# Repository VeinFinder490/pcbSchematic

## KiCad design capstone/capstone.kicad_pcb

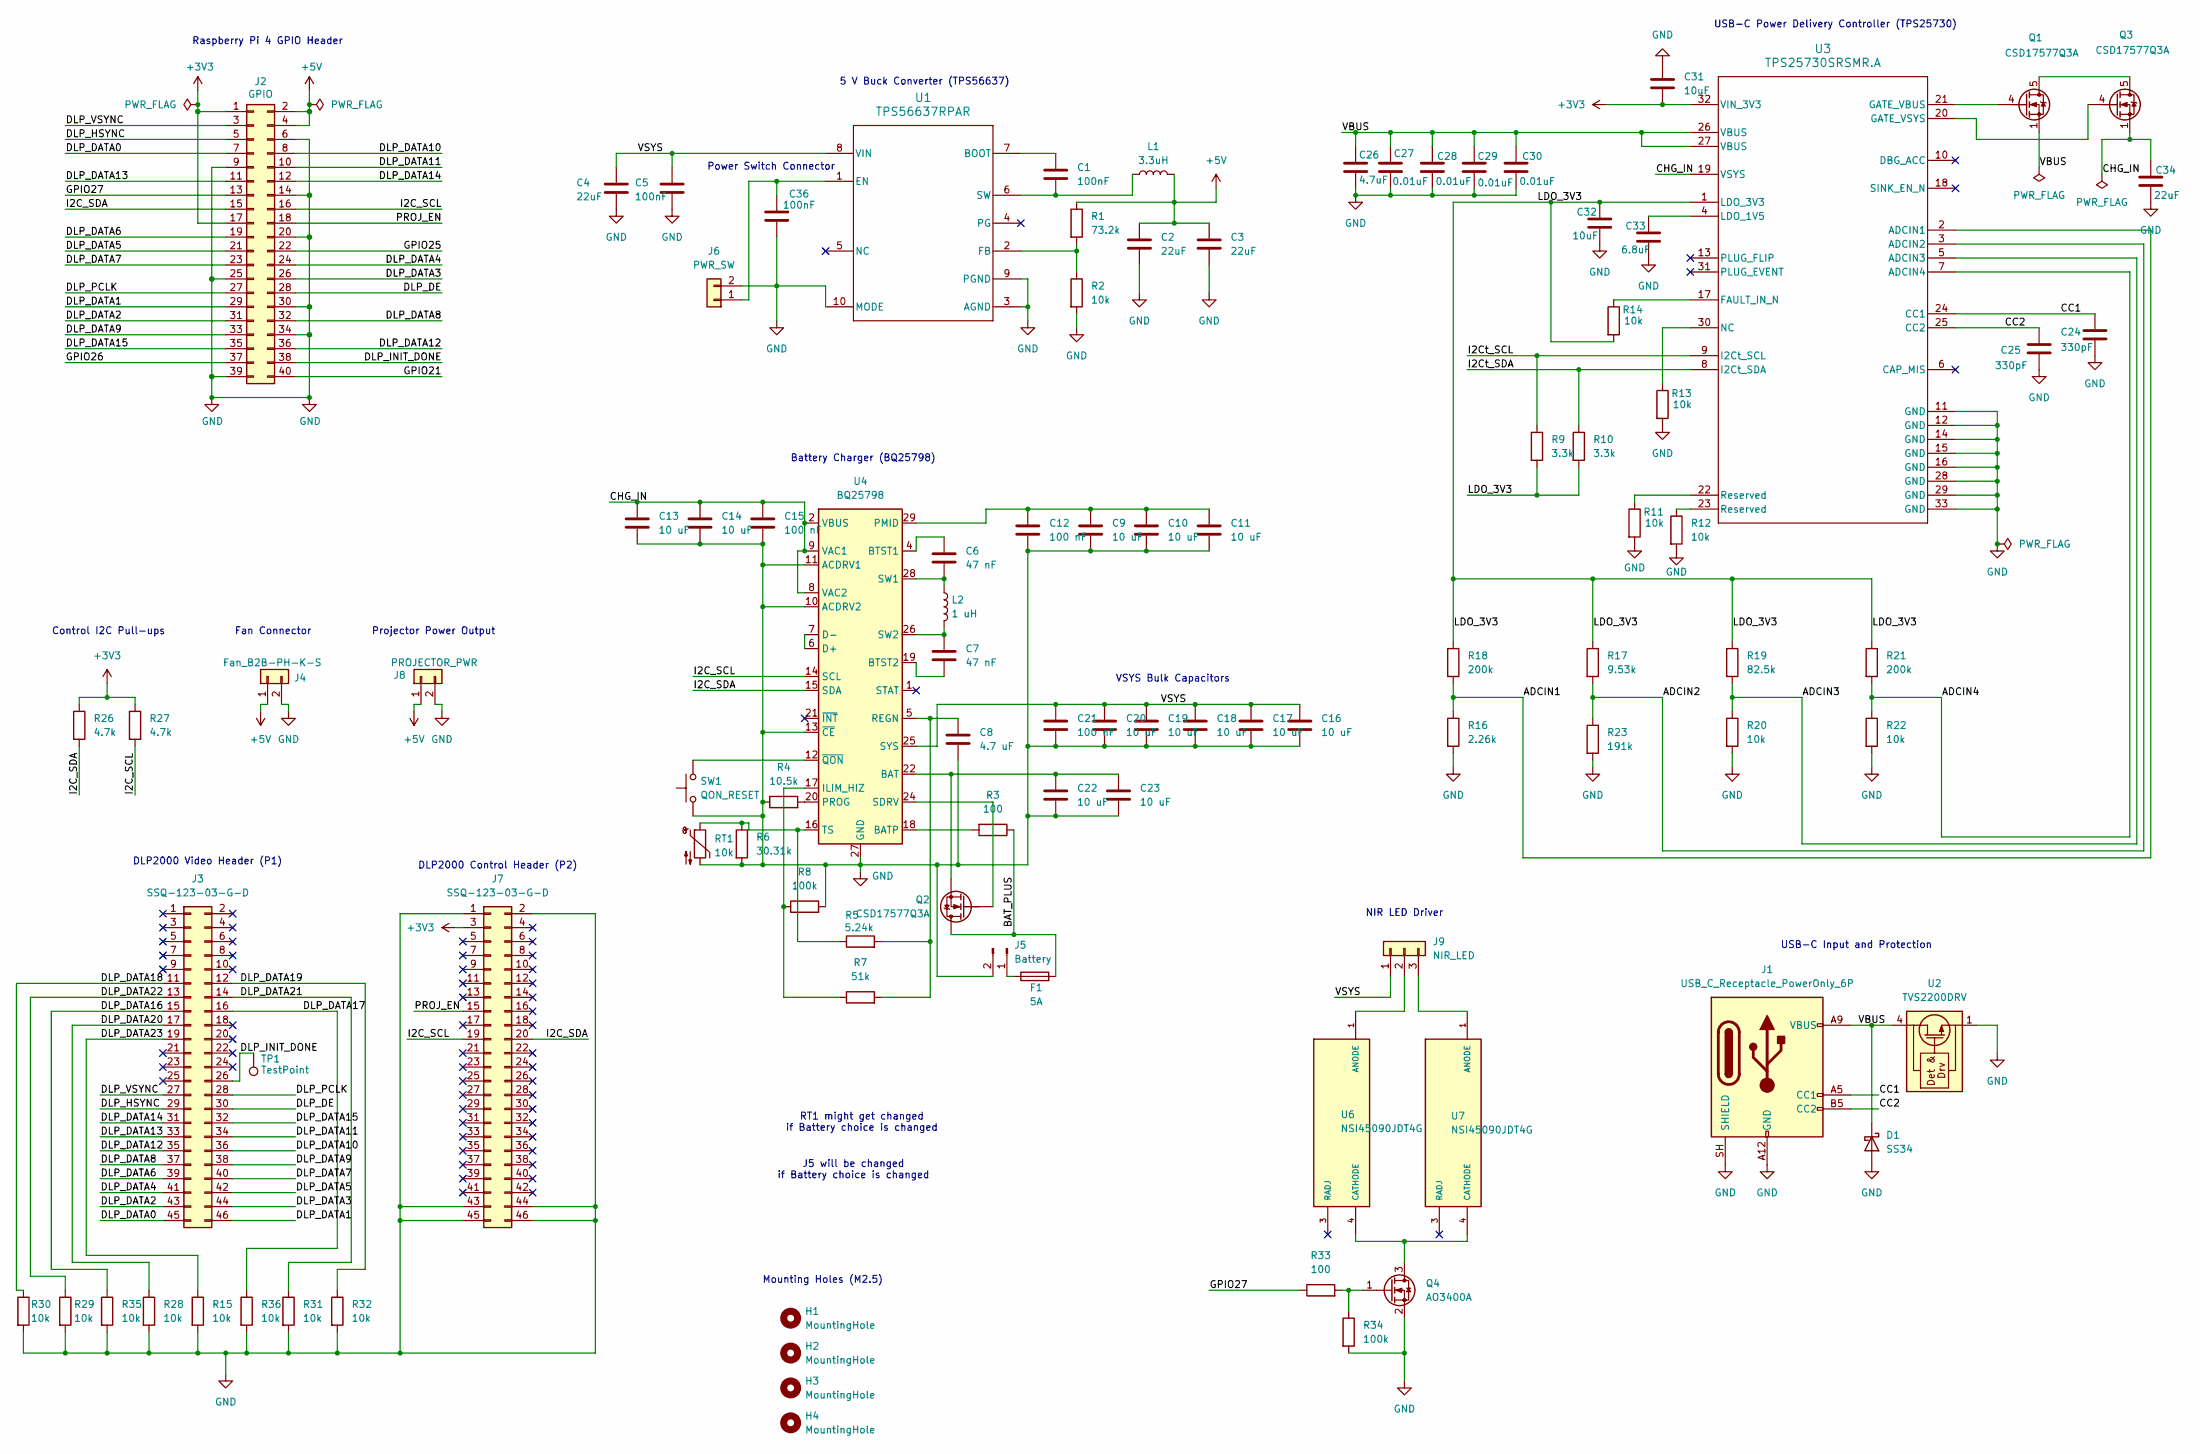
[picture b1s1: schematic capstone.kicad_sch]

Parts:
C1, C5, C36: 100nF; C_0805_2012Metric
C2, C3: 22uF; C_1210_3225Metric
C4, C34: 22uF; C_2220_5750Metric
C6, C7: 47 nF; C_0805_2012Metric
C8: 4.7 uF; C_1206_3216Metric
C9, C10, C11, C13, C14, C16, C17, C18, C19, C20, C22, C23: 10 uF; C_1210_3225Metric
C12, C15, C21: 100 nF; C_0805_2012Metric
C24, C25: 330pF; C_0805_2012Metric
C26: 4.7uF; C_1206_3216Metric
C27, C28, C29, C30: 0.01uF; C_0805_2012Metric
C31, C32: 10uF; C_1210_3225Metric
C33: 6.8uF; C_1206_3216Metric
D1: SS34; D_SMA
F1: 5A; Fuse_1206_3216Metric
H1, H2, H3, H4: MountingHole; MountingHole_2.7mm_M2.5
J1: USB_C_Receptacle_PowerOnly_6P; USB_C_Receptacle_GCT_USB4125-xx-x_6P_TopMnt_Horizontal
J2: GPIO; PinSocket_2x20_P2.54mm_Vertical
J3, J7: SSQ-123-03-G-D; PinHeader_2x23_P2.54mm_Vertical
J4: Fan_B2B-PH-K-S; JST_PH_B2B-PH-K_1x02_P2.00mm_Vertical
J5: Battery; JST_XH_B2B-XH-A_1x02_P2.50mm_Vertical
J6: PWR_SW; JST_PH_B2B-PH-K_1x02_P2.00mm_Vertical
J8: PROJECTOR_PWR; JST_PH_B2B-PH-K_1x02_P2.00mm_Vertical
J9: NIR_LED; JST_PH_B3B-PH-K_1x03_P2.00mm_Vertical
L1: 3.3uH; L_Coilcraft_XAL7030-332
L2: 1 uH; L_Coilcraft_XAL7030-102
Q1, Q2, Q3: CSD17577Q3A; VSON-8_3.3x3.3mm_P0.65mm_NexFET
Q4: AO3400A; SOT-23
R1: 73.2k; R_0805_2012Metric
R2, R11, R12, R13, R14, R15, R20, R22, R28, R29, R30, R31, R32, R35, R36: 10k; R_0805_2012Metric
R3, R33: 100; R_0805_2012Metric
R4: 10.5k; R_0805_2012Metric
R5: 5.24k; R_0805_2012Metric
R6: 30.31k; R_0805_2012Metric
R7: 51k; R_0805_2012Metric
R8, R34: 100k; R_0805_2012Metric
R9, R10: 3.3k; R_0805_2012Metric
R16: 2.26k; R_0805_2012Metric
R17: 9.53k; R_0805_2012Metric
R18, R21: 200k; R_0805_2012Metric
R19: 82.5k; R_0805_2012Metric
R23: 191k; R_0805_2012Metric
R26, R27: 4.7k; R_0805_2012Metric
RT1: 10k; R_0603_1608Metric
SW1: QON_RESET; SW_SPST_PTS645Sx43SMTR92
TP1: TestPoint; TestPoint_Pad_D1.5mm
U1: TPS56637RPAR; RPA0010A
U2: TVS2200DRV; WSON-6-1EP_2x2mm_P0.65mm_EP1x1.6mm
U3: TPS25730SRSMR.A; RSM0032B-IPC_A
U4: BQ25798; Texas_RQM0029A_VQFN-29_4x4mm_P0.4mm
U6, U7: NSI45090JDT4G; IC_NSI45090JDT4G; MPN NSI45090JDT4G

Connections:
+3V3: C31.2, J2.1, J2.17, J7.3, R26.1, R27.1, U3.32 (VIN_3V3)
+5V: C2.1, C3.1, J2.2, J2.4, J4.1, J8.1, L1.2, R1.1
/ADCIN1: R16.1, R18.2, U3.2 (ADCIN1)
/ADCIN2: R17.2, R23.1, U3.3 (ADCIN2)
/ADCIN3: R19.2, R20.1, U3.5 (ADCIN3)
/ADCIN4: R21.2, R22.1, U3.7 (ADCIN4)
/BAT_PLUS: F1.2, Q2.5 (D), R3.1
/CC1: C24.2, J1.A5 (CC1), U3.24 (CC1)
/CC2: C25.2, J1.B5 (CC2), U3.25 (CC2)
/CHG_IN: C13.1, C14.1, C15.1, C34.1, Q3.1 (S), Q3.2 (S), Q3.3 (S), U3.19 (VSYS), U4.2 (VBUS), U4.3 (VBUS), U4.8 (VAC2), U4.9 (VAC1)
/DLP_DATA0: J2.7, J3.45
/DLP_DATA1: J2.29, J3.46
/DLP_DATA2: J2.31, J3.43
/DLP_DATA3: J2.26, J3.44
/DLP_DATA4: J2.24, J3.41
/DLP_DATA5: J2.21, J3.42
/DLP_DATA6: J2.19, J3.39
/DLP_DATA7: J2.23, J3.40
/DLP_DATA8: J2.32, J3.37
/DLP_DATA9: J2.33, J3.38
/DLP_DATA10: J2.8, J3.36
/DLP_DATA11: J2.10, J3.34
/DLP_DATA12: J2.36, J3.35
/DLP_DATA13: J2.11, J3.33
/DLP_DATA14: J2.12, J3.31
/DLP_DATA15: J2.35, J3.32
/DLP_DATA16: J3.15, R35.1
/DLP_DATA17: J3.16, R36.1
/DLP_DATA18: J3.11, R30.1
/DLP_DATA19: J3.12, R32.1
/DLP_DATA20: J3.17, R28.1
/DLP_DATA21: J3.14, R31.1
/DLP_DATA22: J3.13, R29.1
/DLP_DATA23: J3.19, R15.1
/DLP_DE: J2.28, J3.30
/DLP_HSYNC: J2.5, J3.29
/DLP_PCLK: J2.27, J3.28
/DLP_VSYNC: J2.3, J3.27
/GPIO21: J2.40
/GPIO25: J2.22
/GPIO26: J2.37
/GPIO27: J2.13, R33.1
/I2C_SCL: J2.16, J7.19, R27.2, U4.14 (SCL)
/I2C_SDA: J2.15, J7.20, R26.2, U4.15 (SDA)
/I2Ct_SCL: R9.1, U3.9 (I2Ct_SCL)
/I2Ct_SDA: R10.1, U3.8 (I2Ct_SDA)
/LDO_3V3: C32.2, R9.2, R10.2, R14.2, R17.1, R18.1, R19.1, R21.1, U3.1 (LDO_3V3)
/PROJ_EN: J2.18, J7.15
/VBUS: C26.1, C27.1, C28.1, C29.1, C30.1, D1.1 (K), J1.A9 (VBUS), J1.B9 (VBUS), Q1.1 (S), Q1.2 (S), Q1.3 (S), U2.4 (IN), U2.5 (IN), U2.6 (IN), U3.26 (VBUS), U3.27 (VBUS)
/VSYS: C4.1, C5.1, C16.1, C17.1, C18.1, C19.1, C20.1, C21.1, J9.1, U1.8 (VIN), U4.25 (SYS)
GND: C2.2, C3.2, C4.2, C5.2, C8.2, C9.2, C10.2, C11.2, C12.2, C13.2, C14.2, C15.2, C16.2, C17.2, C18.2, C19.2, C20.2, C21.2, C22.2, C23.2, C24.1, C25.1, C26.2, C27.2, C28.2, C29.2, C30.2, C31.1, C32.1, C33.1, C34.2, C36.1, D1.2 (A), J1.A12 (GND), J1.B12 (GND), J1.SH (SHIELD), J2.6, J2.9, J2.14, J2.20, J2.25, J2.30, J2.34, J2.39, J4.2, J5.2, J6.2, J7.1, J7.2, J7.43, J7.44, J7.45, J7.46, J8.2, Q4.2 (S), R2.2, R4.1, R6.2, R8.2, R11.2, R12.2, R13.2, R15.2, R16.2, R20.2, R22.2, R23.2, R28.2, R29.2, R30.2, R31.2, R32.2, R34.2, R35.2, R36.2, RT1.2, SW1.1, U1.3 (AGND), U1.9 (PGND), U1.10 (MODE), U2.1 (GND), U2.2 (GND), U2.3 (GND), U2.7 (GND), U3.11 (GND), U3.12 (GND), U3.14 (GND), U3.15 (GND), U3.16 (GND), U3.28 (GND), U3.29 (GND), U3.33 (GND), U4.10 (ACDRV2), U4.11 (ACDRV1), U4.13 (~CE), U4.27 (GND)
unnamed: C22.1, C23.1, Q2.1 (S), Q2.2 (S), Q2.3 (S), U4.22 (BAT), U4.23 (BAT)
unnamed: F1.1, J5.1
unnamed: C36.2, J6.1, U1.1 (EN)
unnamed: J9.2, U6.1 (ANODE)
unnamed: J9.3, U7.1 (ANODE)
unnamed: Q1.5 (D), Q3.5 (D)
unnamed: Q1.4 (G), U3.21 (GATE_VBUS)
unnamed: Q2.4 (G), U4.24 (SDRV)
unnamed: Q3.4 (G), U3.20 (GATE_VSYS)
unnamed: Q4.3 (D), U6.4 (CATHODE), U7.4 (CATHODE)
unnamed: Q4.1 (G), R33.2, R34.1
unnamed: R11.1, U3.22 (Reserved)
unnamed: R12.1, U3.23 (Reserved)
unnamed: C1.1, U1.7 (BOOT)
unnamed: R1.2, R2.1, U1.2 (FB)
unnamed: C1.2, L1.1, U1.6 (SW)
unnamed: R14.1, U3.17 (FAULT_IN_N)
unnamed: C33.2, U3.4 (LDO_1V5)
unnamed: R13.1, U3.30 (NC)
unnamed: R3.2, U4.18 (BATP)
unnamed: C6.1, U4.4 (BTST1)
unnamed: C7.2, U4.19 (BTST2)
unnamed: R7.1, R8.1, U4.17 (ILIM_HIZ)
unnamed: C9.1, C10.1, C11.1, C12.1, U4.29 (PMID)
unnamed: R4.2, U4.20 (PROG)
unnamed: C8.1, R5.2, R7.2, U4.5 (REGN)
unnamed: C6.2, L2.1, U4.28 (SW1)
unnamed: C7.1, L2.2, U4.26 (SW2)
unnamed: R5.1, R6.1, RT1.1, U4.16 (TS)
unnamed: SW1.2, U4.12 (~QON)

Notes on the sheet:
Power Switch Connector
NIR LED Driver
USB-C Input and Protection
Mounting Holes (M2.5)
Battery Charger (BQ25798)
J5 will be changed if Battery choice is changed
Fan Connector
USB-C Power Delivery Controller (TPS25730)
Raspberry Pi 4 GPIO Header
Control I2C Pull-ups
VSYS Bulk Capacitors
RT1 might get changed if Battery choice is changed
DLP2000 Control Header (P2)
DLP2000 Video Header (P1)
5 V Buck Converter (TPS56637)
Projector Power Output

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
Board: 2 copper layers, 99 parts (1 on the bottom side), 79 nets, no tracks yet.

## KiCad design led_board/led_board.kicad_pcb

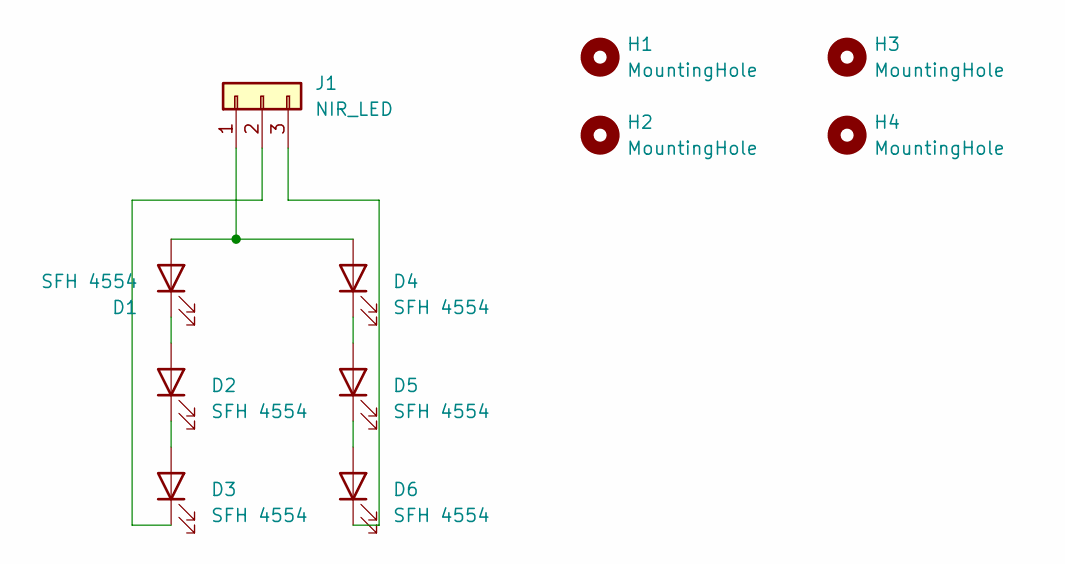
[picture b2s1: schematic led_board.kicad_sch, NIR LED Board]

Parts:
D1, D2, D3, D4, D5, D6: SFH 4554; LED_D5.0mm
H1, H2, H3, H4: MountingHole; MountingHole_2.2mm_M2
J1: NIR_LED; JST_PH_B3B-PH-K_1x03_P2.00mm_Vertical

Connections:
unnamed: D1.2 (A), D4.2 (A), J1.1
unnamed: D1.1 (K), D2.2 (A)
unnamed: D2.1 (K), D3.2 (A)
unnamed: D3.1 (K), J1.2
unnamed: D4.1 (K), D5.2 (A)
unnamed: D5.1 (K), D6.2 (A)
unnamed: D6.1 (K), J1.3

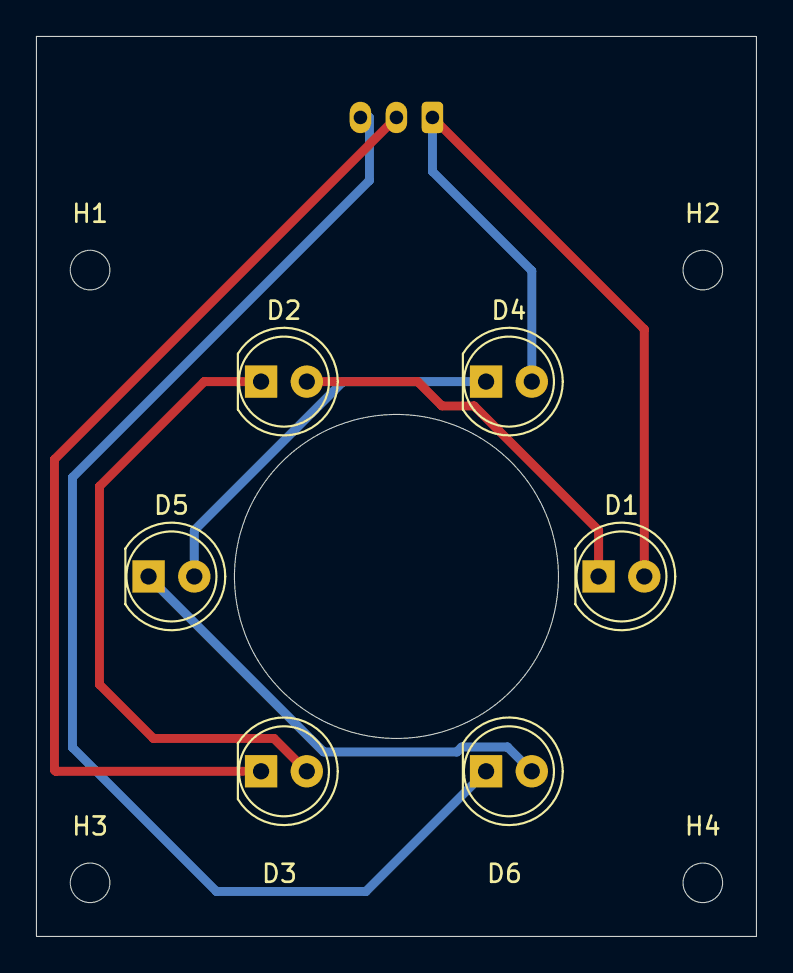
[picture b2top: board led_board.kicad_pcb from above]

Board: 2 copper layers, 40.0 x 50.0 mm, 11 parts (1 on the bottom side), 7 nets.
